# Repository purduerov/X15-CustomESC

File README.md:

# Readme for X15-CustomESC

Whenever you make a new part, download the datasheet and save it here _**and**_ with the part in the parts library

Always pull other people's changes before beginning to work
`git pull`

Be sure to push your changes after  working on them. Run:
1. `git add .` to add any files in this directory or a subdirectory
or `git add -u` to add any modified files
2. (Optional) `git clean -nX` to see what ignored files can be removed
	`git clean -fX` removes ignored files (Eagle backups)
3. `git commit -m "helpful commit message"` with a description of the work that you did
4. `git push` to push your work to github

Other helpful commands
* `git status` says information about modified and staged files
* `git log` shows the recent commits of the repository
* `git log filename.extension` show the recent commits for just that file
* `git checkout first-couple-letter-of-commit-id` lets you go back to a previous version
* `git checkout master` brings you back to the latest commit
* `git tag` lists the tags
* `git tag -a orderX -m "the version of the board placed for the X'th order"` tag a specific commit
* `git push --tags` needed to push tags to remote
* `git show orderX` show the commit log for the given tag
* `git checkout orderX` go back and interact with the files at the tagged commit

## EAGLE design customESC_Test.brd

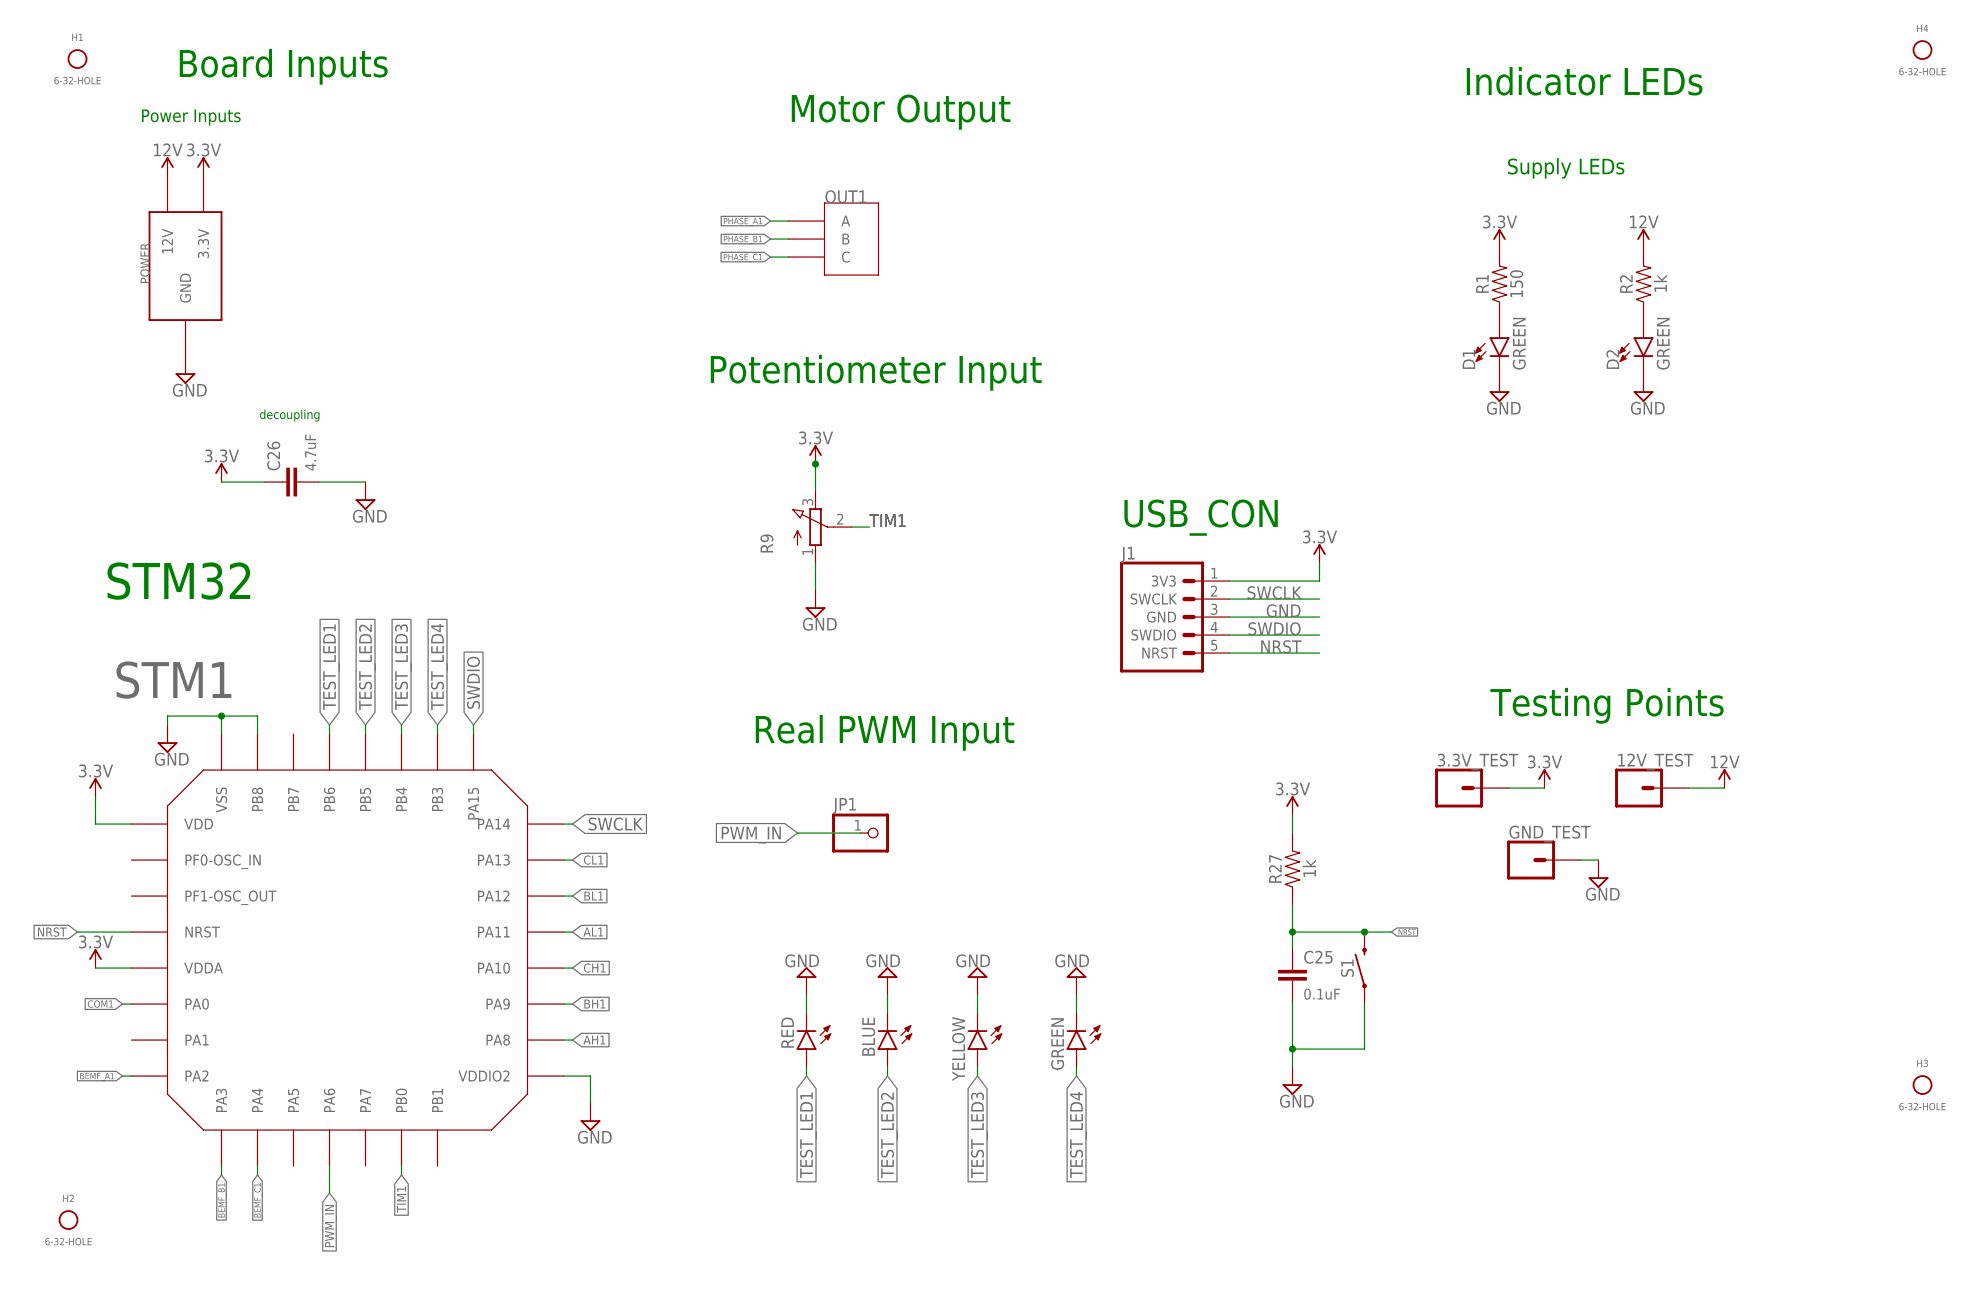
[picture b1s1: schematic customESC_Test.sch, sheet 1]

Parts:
3.3V_TEST, 12V_TEST: CONN_01; 1X01
BLUE: LEDCHIPLED_0805; CHIPLED_0805
C25: 0.1uF; 0603
C26: 4.7uF; 0603
D1, D2: GREEN; LED-0603
GND_TEST: CONN_01; 1X01
GREEN: LEDCHIPLED_0805; CHIPLED_0805
H1, H2, H3, H4: 6-32-HOLE; MOUNTING_HOLE
J1: 3V3 -SWCLK-GND-SWDIO- NRST; 1X05
JP1: PINHD-1X1; 1X01
OUT1: IPBT-103-H1-T-S
POWER: 12V-CONNECTOR
R1: 150; 0603
R2, R27: 1k; 0603
R9: 3RP/1610N
RED: LEDCHIPLED_0805; CHIPLED_0805
S1: MOMENTARY-SWITCH-SPST-SMD-6.0X3.5MM; TACTILE_SWITCH_SMD_6.0X3.5MM
STM1: STM32F042K6T6
YELLOW: LEDCHIPLED_0805; CHIPLED_0805

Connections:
AH1: STM1.PA8; also elsewhere on the board
AL1: STM1.PA11; also elsewhere on the board
BEMF_A1: STM1.PA2; also elsewhere on the board
BEMF_B1: STM1.PA3; also elsewhere on the board
BEMF_C1: STM1.PA4; also elsewhere on the board
BH1: STM1.PA9; also elsewhere on the board
BL1: STM1.PA12; also elsewhere on the board
CH1: STM1.PA10; also elsewhere on the board
CL1: STM1.PA13; also elsewhere on the board
COM1: STM1.PA0; also elsewhere on the board
GND: BLUE.C, C25.2, C26.2, D1.C, D2.C, GND_TEST.1, GREEN.C, J1.3 (GND), POWER.GND, POWER.GND@1 (GND), POWER.GND@2 (GND), POWER.GND@3 (GND), POWER.GND@4 (GND), POWER.GND@5 (GND), POWER.GND@6 (GND), POWER.GND@7 (GND), POWER.GND@8 (GND), POWER.GND@9 (GND), POWER.GND@10 (GND), POWER.GND@11 (GND), POWER.GND@12 (GND), R9.1 (A), RED.C, S1.1, STM1.PB8-BOOT0 (PB8), STM1.VDDIO2, STM1.VSS, STM1.VSS1 (VSS), YELLOW.C; also elsewhere on the board
unnamed: D1.A, R1.1
unnamed: D2.A, R2.1
NRST: C25.1, J1.5 (NRST), R27.1, S1.2, STM1.NRST
PHASE_A1: OUT1.1 (A); also elsewhere on the board
PHASE_B1: OUT1.2 (B); also elsewhere on the board
PHASE_C1: OUT1.3 (C); also elsewhere on the board
PWM_IN: JP1.1, STM1.PA6
SWCLK: J1.2 (SWCLK), STM1.PA14
SWDIO: J1.4 (SWDIO), STM1.PA15
TEST_LED1: RED.A, STM1.PB6
TEST_LED2: BLUE.A, STM1.PB5
TEST_LED3: STM1.PB4, YELLOW.A
TEST_LED4: GREEN.A, STM1.PB3
TIM1: R9.2 (S), STM1.PB0
VCC_1: 3.3V_TEST.1, C26.1, J1.1 (3V3), POWER.3.3V, R1.2, R9.3 (E), R27.2, STM1.VDD, STM1.VDDA
VCC_2: 12V_TEST.1, POWER.12V@1 (12V), POWER.12V@2 (12V), POWER.12V@3 (12V), POWER.12V@4 (12V), POWER.12V@5 (12V), POWER.12V@6 (12V), POWER.12V@7 (12V), POWER.12V@8 (12V), POWER.12V@9 (12V), POWER.12V@10 (12V), POWER.12V@11 (12V), POWER.12V@12 (12V), R2.2; also elsewhere on the board

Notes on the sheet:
Supply LEDs
Power Inputs
Motor Output
STM32
decoupling
Indicator LEDs
Testing Points
Board Inputs
Potentiometer Input
Real PWM Input
USB_CON

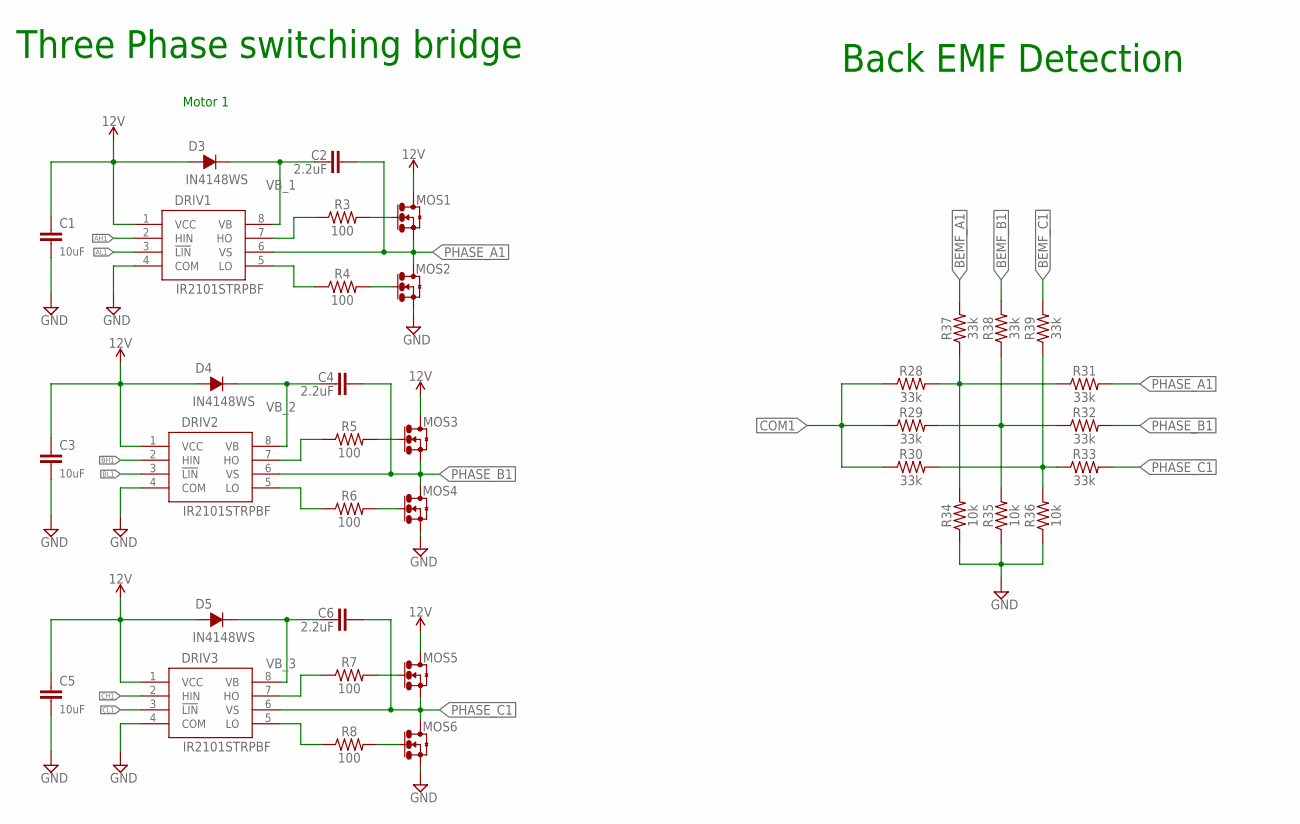
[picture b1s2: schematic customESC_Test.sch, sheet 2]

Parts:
C1, C3, C5: 10uF; 0603
C2, C4, C6: 2.2uF; 0603
D3, D4, D5: IN4148WS
DRIV1, DRIV2, DRIV3: IR2101STRPBF
MOS1, MOS2, MOS3, MOS4, MOS5, MOS6: IRLR7843TRPBF
R3, R4, R5, R6, R7, R8: 100; 0603
R28, R29, R30, R31, R32, R33, R37, R38, R39: 33k; 0603
R34, R35, R36: 10k; 0603

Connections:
AH1: DRIV1.2 (HIN); also elsewhere on the board
AL1: DRIV1.3 (!LIN); also elsewhere on the board
BEMF_A1: R37.2; also elsewhere on the board
BEMF_B1: R38.2; also elsewhere on the board
BEMF_C1: R39.2; also elsewhere on the board
BH1: DRIV2.2 (HIN); also elsewhere on the board
BL1: DRIV2.3 (!LIN); also elsewhere on the board
CH1: DRIV3.2 (HIN); also elsewhere on the board
CL1: DRIV3.3 (!LIN); also elsewhere on the board
COM1: R28.1, R29.1, R30.1; also elsewhere on the board
GND: C1.2, C3.2, C5.2, DRIV1.4 (COM), DRIV2.4 (COM), DRIV3.4 (COM), MOS2.2 (DRAIN), MOS2.4 (DRAIN), MOS4.2 (DRAIN), MOS4.4 (DRAIN), MOS6.2 (DRAIN), MOS6.4 (DRAIN), R34.1, R35.1, R36.1; also elsewhere on the board
unnamed: DRIV1.7 (HO), R3.1
unnamed: MOS1.1 (GATE), R3.2
unnamed: DRIV1.5 (LO), R4.1
unnamed: MOS2.1 (GATE), R4.2
unnamed: DRIV2.7 (HO), R5.1
unnamed: DRIV2.5 (LO), R6.1
unnamed: MOS3.1 (GATE), R5.2
unnamed: MOS4.1 (GATE), R6.2
unnamed: DRIV3.7 (HO), R7.1
unnamed: DRIV3.5 (LO), R8.1
unnamed: MOS5.1 (GATE), R7.2
unnamed: MOS6.1 (GATE), R8.2
unnamed: R28.2, R31.1, R34.2, R37.1
unnamed: R29.2, R32.1, R35.2, R38.1
unnamed: R30.2, R33.1, R36.2, R39.1
PHASE_A1: C2.2, DRIV1.6 (VS), MOS1.2 (DRAIN), MOS1.4 (DRAIN), MOS2.3 (SOURCE), R31.2; also elsewhere on the board
PHASE_B1: C4.2, DRIV2.6 (VS), MOS3.2 (DRAIN), MOS3.4 (DRAIN), MOS4.3 (SOURCE), R32.2; also elsewhere on the board
PHASE_C1: C6.2, DRIV3.6 (VS), MOS5.2 (DRAIN), MOS5.4 (DRAIN), MOS6.3 (SOURCE), R33.2; also elsewhere on the board
VB_1: C2.1, D3.P$2, DRIV1.8 (VB)
VB_2: C4.1, D4.P$2, DRIV2.8 (VB)
VB_3: C6.1, D5.P$2, DRIV3.8 (VB)
VCC_2: C1.1, C3.1, C5.1, D3.P$1, D4.P$1, D5.P$1, DRIV1.1 (VCC), DRIV2.1 (VCC), DRIV3.1 (VCC), MOS1.3 (SOURCE), MOS3.3 (SOURCE), MOS5.3 (SOURCE); also elsewhere on the board

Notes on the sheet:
Three Phase switching bridge
Motor 1
Back EMF Detection

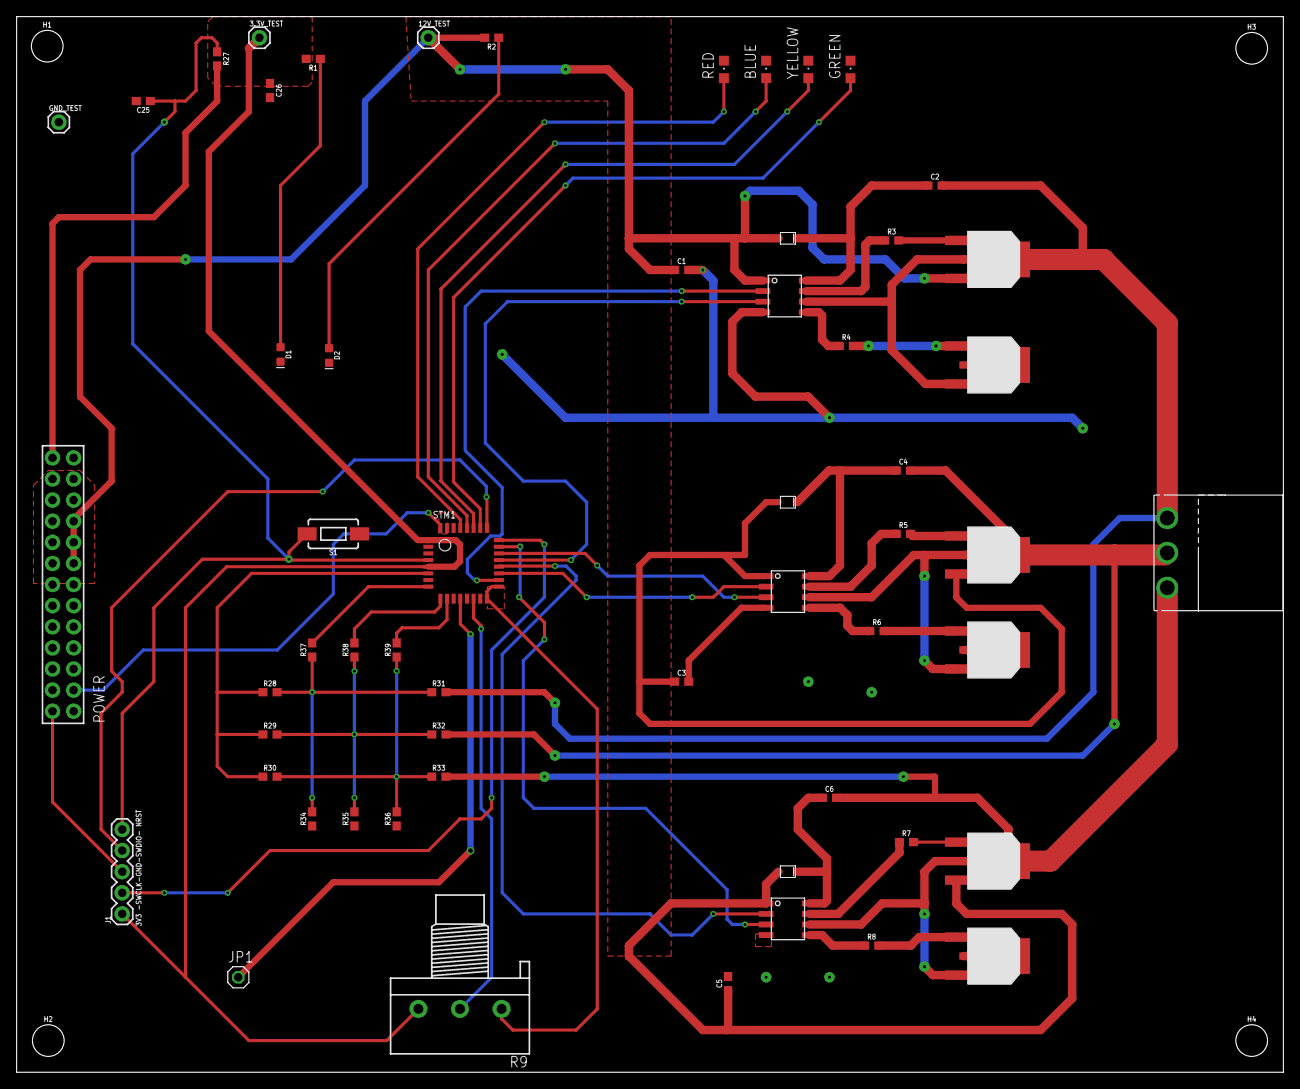
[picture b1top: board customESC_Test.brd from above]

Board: 2 copper layers, 152.4 x 127.0 mm, 61 parts (0 on the bottom side), 45 nets.

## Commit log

2022-10-22 Started the schematic
2022-11-10 Made some progress on schematic
2022-11-12 Ready for design review? not really
2022-11-12 Finished main schematic
2022-11-17 Added a new file
2022-11-17 change name
2022-11-17 name change
2022-12-01 update
    lol
2022-12-03 IM DOING WORK AT 4AM
    I LOVE ROV!!!!!!!!!!!!!!!!!!!!!!!!!!!!!!!!!!!!!!!!!!!!
2022-12-03 Catherine Check off
    Hello
2022-12-04 Finished first draft
    Need a design review before ordering
2022-12-08 Fixed issues from design review
2023-01-21 added paths for input and added test leds. needs a design review
2023-01-26 done
2023-01-26 last one
2023-02-09 Yusuf, check review_notes.txt
2023-02-11 updates on supply line and moved the leds and reset button
2023-03-02 Fixed it Raghav
    Hi

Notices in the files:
parts and their libraries:
SparkFun-Connectors: Licensing: Creative Commons ShareAlike 4.0 International - https://creativecommons.org/licenses/by-sa/4.0
